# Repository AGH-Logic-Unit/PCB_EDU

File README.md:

# Educational Board by AGH Logic Unit

An educational PCB board that demonstrates the architecture and operating principles of a processor in a highly simplified way. The project allows you to physically trace the data flow between memory, registers, and logic. All signals are controlled manually, and logic states are visualized in real time across the respective sections using LEDs.

## Functional Blocks

The system is divided into several sections:
* **Instruction Memory** - a set of LEDs reflecting the current state of the switches on the bottom panel (input data, selected register addresses, operation code).
* **Register File** - memory implemented as a 4x4 LED matrix. It represents 4 registers of 4 bits each. The LED arrangement allows direct observation of data distribution in the memory. By manipulating the inputs, you can also manually draw simple shapes on the matrix.
* **ALU** - an asynchronous, simplified arithmetic logic unit performing bitwise operations on the data fetched from the registers.
* **Data Memory** - output LEDs displaying the final result of the operation performed by the ALU.

## Interface and Controls

On the bottom edge of the board, there is a panel equipped with toggle switches and push buttons. 

Meaning of the individual signals:
* `DATA [3..0]` - sets the 4 data bits to be introduced into the system.
* `R SET [1..0]` - (Register Set) selects the address of one of the 4 registers where the value from the DATA lines will be written.
* `REG 0 [1..0]` - address of the first source register. Data from this register is routed to the first input of the ALU.
* `REG 1 [1..0]` - address of the second source register. Data from this register is routed to the second input of the ALU.
* `OP` - selects the type of logical operation performed by the ALU (AND or OR).
* `WE` - (Write Enable) a push button triggering the write process. Pressing it saves the current state of the DATA lines to the register indicated by R SET.
* `RST` - asynchronous reset button. Clears the contents of all registers (zeroes the matrix).
* `LED` - a switch used to demonstrate the Two's complement (U2) format.

## Basic Data Flow (Example)

1. Set a specific value on the `DATA` switches.
2. Use the `R SET` switch to indicate the register you want to write to (e.g., address 00).
3. Click `WE`, which immediately lights up the corresponding LEDs in the first row of the Register File block.
4. Change the `DATA` value, set `R SET` to the next register (e.g., 01), and write it again by pressing `WE`.
5. Route the saved data to the ALU: set `REG 0` to address 00 and `REG 1` to address 01.
6. Use the `OP` switch to decide whether an AND or OR operation should be performed on the given inputs.
7. The Data Memory section will display the operation's result.

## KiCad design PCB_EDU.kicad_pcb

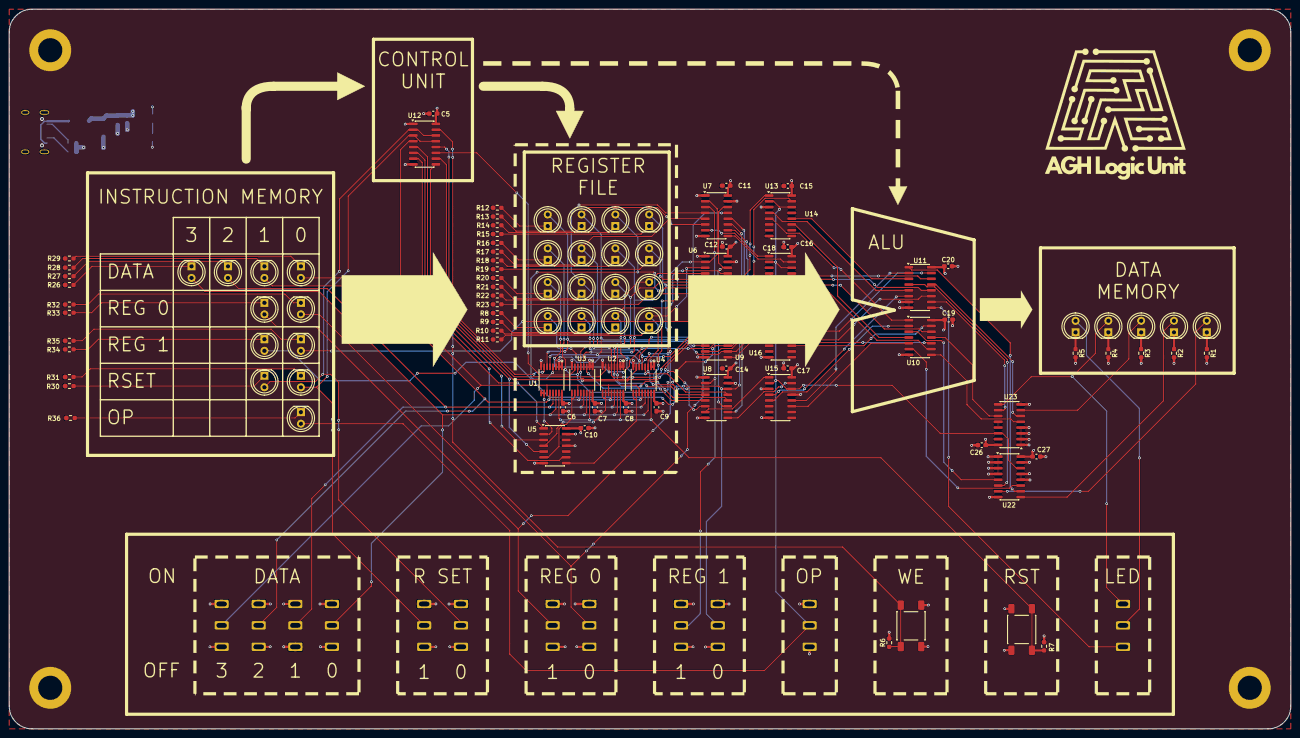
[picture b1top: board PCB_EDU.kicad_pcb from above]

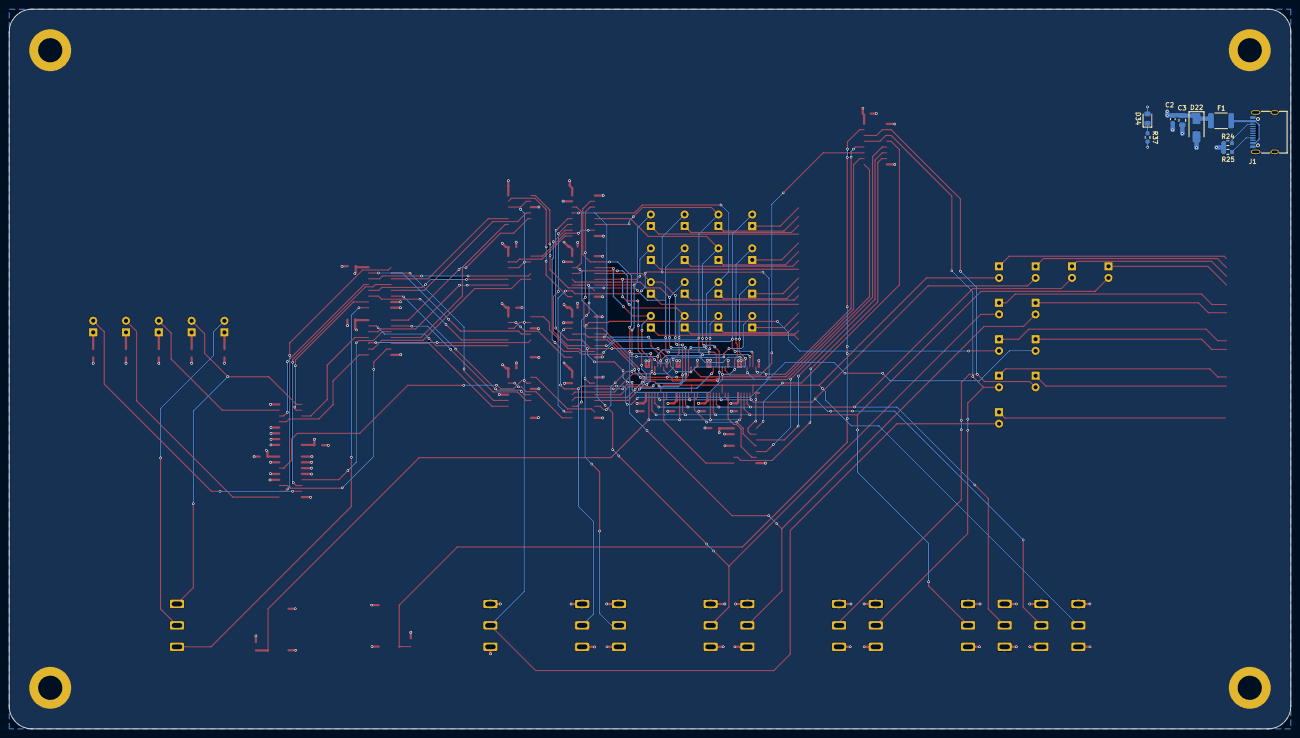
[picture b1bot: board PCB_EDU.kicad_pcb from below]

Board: 4 copper layers, 281.2 x 157.9 mm, 129 parts (9 on the bottom side), 117 nets.

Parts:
C2, C5, C6, C7, C8, C9, C10, C11, C12, C13, C14, C15, C16, C17, C18, C19, C20, C26, C27: 100n; C_0603_1608Metric_Pad1.08x0.95mm_HandSolder
C3: 10u; C_0805_2012Metric_Pad1.18x1.45mm_HandSolder
D1, D2, D3, D4, D5, D6, D7, D8, D9, D10, D11, D12, D13, D14, D15, D16, D17, D18, D19, D20, D21, D23, D24, D25, D26, D27, D28, D29, D30, D31, D32, D33: LED; LED_D5.0mm
D22: SMAJ5.0A; D_SMA
D34: LED; LED_0805_2012Metric_Pad1.15x1.40mm_HandSolder
F1: PPTC; Fuse_1812_4532Metric_Pad1.30x3.40mm_HandSolder
H1, H2, H3, H4: MH_P; MountingHole_5.3mm_M5_DIN965_Pad
J1: USB_C_16_PIN; USB_C_Receptacle_G-Switch_GT-USB-7010ASV
R1, R2, R3, R4, R5, R8, R9, R10, R11, R12, R13, R14, R15, R16, R17, R18, R19, R20, R21, R22, R23, R26, R27, R28, R29, R30, R31, R32, R33, R34, R35, R36, R37: 1k; R_0603_1608Metric_Pad0.98x0.95mm_HandSolder
R6, R7: 10k; R_0603_1608Metric_Pad0.98x0.95mm_HandSolder
R24, R25: 5.1k; R_0603_1608Metric_Pad0.98x0.95mm_HandSolder
SW1, SW14, SW15, SW16, SW17, SW18, SW19, SW20, SW21, SW22, SW23, SW24: SW_SPDT; SPDT_switch
SW2, SW3: SW_Push; SW_Push_1P1T_NO_E-Switch_TL3301NxxxxxG
U1, U2, U3, U4: 74HC173; TSSOP-16_4.4x5mm_P0.65mm
U5: 74HC04; SOIC-14_3.9x8.7mm_P1.27mm
U6, U7, U8, U9, U22, U23: 74LS153; SOIC-16_3.9x9.9mm_P1.27mm
U10: 74LS32; SOIC-14_3.9x8.7mm_P1.27mm
U11: 74LS283; SOIC-16_3.9x9.9mm_P1.27mm
U12, U13, U14, U15, U16: 74LS139; SOIC-16_3.9x9.9mm_P1.27mm

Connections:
/1-2_demux_x4_1/X0: U6.7 (Za), U13.1 (E)
/1-2_demux_x4_1/X1: U6.9 (Zb), U13.15 (E)
/1-2_demux_x4_1/X2: U7.7 (Za), U14.1 (E)
/1-2_demux_x4_1/X3: U7.9 (Zb), U14.15 (E)
/1-2_demux_x4_2/X0: U8.7 (Za), U15.1 (E)
/1-2_demux_x4_2/X1: U8.9 (Zb), U15.15 (E)
/1-2_demux_x4_2/X2: U9.7 (Za), U16.1 (E)
/1-2_demux_x4_2/X3: U9.9 (Zb), U16.15 (E)
/1_R0: D13.2 (A), U1.3 (Q0), U6.6 (I0a), U8.6 (I0a)
/1_R1: D12.2 (A), U1.4 (Q1), U6.10 (I0b), U8.10 (I0b)
/1_R2: D11.2 (A), U1.5 (Q2), U7.6 (I0a), U9.6 (I0a)
/1_R3: D10.2 (A), U1.6 (Q3), U7.10 (I0b), U9.10 (I0b)
/1_Y0: U11.5 (A1), U13.4 (O0)
/1_Y1: U10.1, U13.5 (O1)
/2_R0: D17.2 (A), U3.3 (Q0), U6.5 (I1a), U8.5 (I1a)
/2_R1: D16.2 (A), U3.4 (Q1), U6.11 (I1b), U8.11 (I1b)
/2_R2: D15.2 (A), U3.5 (Q2), U7.5 (I1a), U9.5 (I1a)
/2_R3: D14.2 (A), U3.6 (Q3), U7.11 (I1b), U9.11 (I1b)
/2_Y0: U11.3 (A2), U13.12 (O0)
/2_Y1: U10.4, U13.11 (O1)
/3_R0: D21.2 (A), U2.3 (Q0), U6.4 (I2a), U8.4 (I2a)
/3_R1: D20.2 (A), U2.4 (Q1), U6.12 (I2b), U8.12 (I2b)
/3_R2: D19.2 (A), U2.5 (Q2), U7.4 (I2a), U9.4 (I2a)
/3_R3: D18.2 (A), U2.6 (Q3), U7.12 (I2b), U9.12 (I2b)
/3_Y0: U11.14 (A3), U14.4 (O0)
/3_Y1: U10.9, U14.5 (O1)
/4_R0: D9.2 (A), U4.3 (Q0), U6.3 (I3a), U8.3 (I3a)
/4_R1: D8.2 (A), U4.4 (Q1), U6.13 (I3b), U8.13 (I3b)
/4_R2: D7.2 (A), U4.5 (Q2), U7.3 (I3a), U9.3 (I3a)
/4_R3: D6.2 (A), U4.6 (Q3), U7.13 (I3b), U9.13 (I3b)
/4_Y0: U11.12 (A4), U14.12 (O0)
/4_Y1: U10.12, U14.11 (O1)
/5_Y0: U11.6 (B1), U15.4 (O0)
/5_Y1: U10.2, U15.5 (O1)
/6_Y0: U11.2 (B2), U15.12 (O0)
/6_Y1: U10.5, U15.11 (O1)
/7_Y0: U11.15 (B3), U16.4 (O0)
/7_Y1: U10.10, U16.5 (O1)
/8_Y0: U11.11 (B4), U16.12 (O0)
/8_Y1: U10.13, U16.11 (O1)
/ADD0: U11.4 (S1), U22.6 (I0a)
/ADD1: U11.1 (S2), U22.10 (I0b)
/ADD2: U11.13 (S3), U23.6 (I0a)
/ADD3: U11.10 (S4), U23.10 (I0b)
/CP0: U1.7 (Cp), U12.12 (O0)
/CP1: U3.7 (Cp), U12.11 (O1)
/CP2: U2.7 (Cp), U12.10 (O2)
/CP3: U4.7 (Cp), U12.9 (O3)
/C_OUT: SW1.1 (A), U11.9 (C4)
/D0: D23.2 (A), SW14.2 (B), U1.14 (D0), U2.14 (D0), U3.14 (D0), U4.14 (D0)
/D1: D24.2 (A), SW15.2 (B), U1.13 (D1), U2.13 (D1), U3.13 (D1), U4.13 (D1)
/D2: D25.2 (A), SW16.2 (B), U1.12 (D2), U2.12 (D2), U3.12 (D2), U4.12 (D2)
/D3: D26.2 (A), SW17.2 (B), U1.11 (D3), U2.11 (D3), U3.11 (D3), U4.11 (D3)
/E0: U5.1, U12.4 (O0)
/E1: U5.5, U12.5 (O1)
/E2: U5.3, U12.6 (O2)
/E3: U5.9, U12.7 (O3)
/LED_OP0: D1.2 (A), U22.7 (Za)
/LED_OP1: D2.2 (A), U22.9 (Zb)
/LED_OP2: D3.2 (A), U23.7 (Za)
/LED_OP3: D4.2 (A), SW1.3 (C), U23.9 (Zb)
/LED_OP4: D5.2 (A), SW1.2 (B)
/OP: D33.2 (A), SW24.2 (B), U13.2 (A0), U13.14 (A0), U14.2 (A0), U14.14 (A0), U15.2 (A0), U15.14 (A0), U16.2 (A0), U16.14 (A0), U22.14 (S0), U23.14 (S0)
/OR0: U10.3, U22.5 (I1a)
/OR1: U10.6, U22.11 (I1b)
/OR2: U10.8, U23.5 (I1a)
/OR3: U10.11, U23.11 (I1b)
/R00: D29.2 (A), SW20.2 (B), U6.14 (S0), U7.14 (S0)
/R01: D30.2 (A), SW21.2 (B), U6.2 (S1), U7.2 (S1)
/R10: D31.2 (A), SW22.2 (B), U8.14 (S0), U9.14 (S0)
/R11: D32.2 (A), SW23.2 (B), U8.2 (S1), U9.2 (S1)
/RSET0: D27.2 (A), SW18.2 (B), U12.2 (A0), U12.14 (A0)
/RSET1: D28.2 (A), SW19.2 (B), U12.3 (A1), U12.13 (A1)
/RST: R7.1, SW3.1, U1.15 (Mr), U2.15 (Mr), U3.15 (Mr), U4.15 (Mr)
/VBUS: F1.1, J1.A4 (VBUS), J1.A9 (VBUS), J1.B4 (VBUS), J1.B9 (VBUS)
/WE: R6.1, SW2.1, U12.15 (E)
GND: C2.2, C3.2, C5.2, C6.2, C7.2, C8.2, C9.2, C10.2, C11.2, C12.2, C13.2, C14.2, C15.2, C16.2, C17.2, C18.2, C19.2, C20.2, C26.2, C27.2, D22.2 (A2), H1.1 (1_1), H2.1 (1_1), H3.1 (1_1), H4.1 (1_1), J1.A1 (GND), J1.A12 (GND), J1.B1 (GND), J1.B12 (GND), J1.SH (SHIELD), R1.2, R2.2, R3.2, R4.2, R5.2, R6.2, R7.2, R8.2, R9.2, R10.2, R11.2, R12.2, R13.2, R14.2, R15.2, R16.2, R17.2, R18.2, R19.2, R20.2, R21.2, R22.2, R23.2, R24.2, R25.2, R26.2, R27.2, R28.2, R29.2, R30.2, R31.2, R32.2, R33.2, R34.2, R35.2, R36.2, R37.2, SW14.1 (A), SW15.1 (A), SW16.1 (A), SW17.1 (A), SW18.1 (A), SW19.1 (A), SW20.1 (A), SW21.1 (A), SW22.1 (A), SW23.1 (A), SW24.1 (A), U1.1 (Oe1), U1.2 (Oe2), U1.8 (GND), U2.1 (Oe1), U2.2 (Oe2), U2.8 (GND), U3.1 (Oe1), U3.2 (Oe2), U3.8 (GND), U4.1 (Oe1), U4.2 (Oe2), U4.8 (GND), U5.7 (GND), U6.1 (Ea), U6.8 (GND), U6.15 (Eb), U7.1 (Ea), U7.8 (GND), U7.15 (Eb), U8.1 (Ea), U8.8 (GND), U8.15 (Eb), U9.1 (Ea), U9.8 (GND), U9.15 (Eb), U10.7 (GND), U11.7 (C0), U11.8 (GND), U12.8 (GND), U13.3 (A1), U13.8 (GND), U13.13 (A1), U14.3 (A1), U14.8 (GND), U14.13 (A1), U15.3 (A1), U15.8 (GND), U15.13 (A1), U16.3 (A1), U16.8 (GND), U16.13 (A1), U22.1 (Ea), U22.2 (S1), U22.3 (I3a), U22.4 (I2a), U22.8 (GND), U22.12 (I2b), U22.13 (I3b), U22.15 (Eb), U23.1 (Ea), U23.2 (S1), U23.3 (I3a), U23.4 (I2a), U23.8 (GND), U23.12 (I2b), U23.13 (I3b), U23.15 (Eb)
unnamed: D1.1 (K), R1.1
unnamed: D2.1 (K), R2.1
unnamed: D3.1 (K), R3.1
unnamed: D4.1 (K), R4.1
unnamed: D5.1 (K), R5.1
unnamed: D6.1 (K), R8.1
unnamed: D7.1 (K), R9.1
unnamed: D8.1 (K), R10.1
unnamed: D9.1 (K), R11.1
unnamed: D10.1 (K), R12.1
unnamed: D11.1 (K), R13.1
unnamed: D12.1 (K), R14.1
unnamed: D13.1 (K), R15.1
unnamed: D14.1 (K), R16.1
unnamed: D15.1 (K), R17.1
unnamed: D16.1 (K), R18.1
unnamed: D17.1 (K), R19.1
unnamed: D18.1 (K), R20.1
unnamed: D19.1 (K), R21.1
unnamed: D20.1 (K), R22.1
unnamed: D21.1 (K), R23.1
unnamed: D23.1 (K), R26.1
unnamed: D24.1 (K), R27.1
unnamed: D25.1 (K), R28.1
unnamed: D26.1 (K), R29.1
unnamed: D27.1 (K), R30.1
unnamed: D28.1 (K), R31.1
unnamed: D29.1 (K), R32.1
unnamed: D30.1 (K), R33.1
unnamed: D31.1 (K), R34.1
unnamed: D32.1 (K), R35.1
unnamed: D33.1 (K), R36.1
unnamed: D34.1 (K), R37.1
unnamed: J1.A5 (CC1), R25.1
unnamed: J1.B5 (CC2), R24.1
unnamed: U1.9 (E1), U1.10 (E2), U5.2
unnamed: U2.9 (E1), U2.10 (E2), U5.4
unnamed: U3.9 (E1), U3.10 (E2), U5.6
unnamed: U4.9 (E1), U4.10 (E2), U5.8
VDD: C2.1, C3.1, C5.1, C6.1, C7.1, C8.1, C9.1, C10.1, C11.1, C12.1, C13.1, C14.1, C15.1, C16.1, C17.1, C18.1, C19.1, C20.1, C26.1, C27.1, D22.1 (A1), D34.2 (A), F1.2, SW2.2, SW3.2, SW14.3 (C), SW15.3 (C), SW16.3 (C), SW17.3 (C), SW18.3 (C), SW19.3 (C), SW20.3 (C), SW21.3 (C), SW22.3 (C), SW23.3 (C), SW24.3 (C), U1.16 (VCC), U2.16 (VCC), U3.16 (VCC), U4.16 (VCC), U5.11, U5.13, U5.14 (VCC), U6.16 (VCC), U7.16 (VCC), U8.16 (VCC), U9.16 (VCC), U10.14 (VCC), U11.16 (VCC), U12.1 (E), U12.16 (VCC), U13.16 (VCC), U14.16 (VCC), U15.16 (VCC), U16.16 (VCC), U22.16 (VCC), U23.16 (VCC)
